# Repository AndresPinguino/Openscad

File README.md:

# Openscad
Modelos 3D parametricos

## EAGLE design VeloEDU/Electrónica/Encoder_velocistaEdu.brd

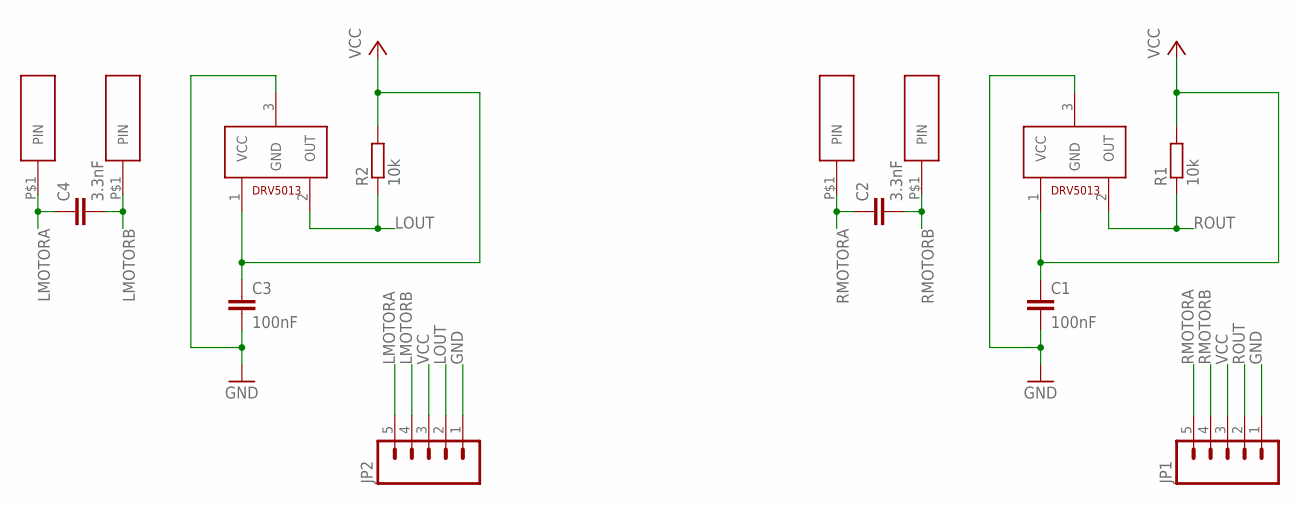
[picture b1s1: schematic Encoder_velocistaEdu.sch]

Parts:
C1, C3: 100nF; C0805
C2, C4: 3.3nF; C0805
JP1, JP2: M05PTH; 1X05
R1, R2: 10k; M0805
U$1, U$6: DRV5013; DBZ_R-PDSO-G3
U$2, U$3, U$4, U$5: TERMINAL_MOTOR_N20

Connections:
GND: C1.2, C3.2, JP1.1, JP2.1, U$1.3 (GND), U$6.3 (GND)
LMOTORA: C4.1, JP2.5, U$4.P$1
LMOTORB: C4.2, JP2.4, U$5.P$1
LOUT: JP2.2, R2.1, U$6.2 (OUT)
RMOTORA: C2.1, JP1.5, U$2.P$1
RMOTORB: C2.2, JP1.4, U$3.P$1
ROUT: JP1.2, R1.1, U$1.2 (OUT)
VCC: C1.1, C3.1, JP1.3, JP2.3, R1.2, R2.2, U$1.1 (VCC), U$6.1 (VCC)

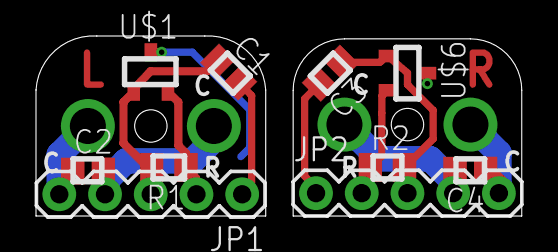
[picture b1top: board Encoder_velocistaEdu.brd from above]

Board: 2 copper layers, 27.0 x 10.0 mm, 14 parts (0 on the bottom side), 8 nets.

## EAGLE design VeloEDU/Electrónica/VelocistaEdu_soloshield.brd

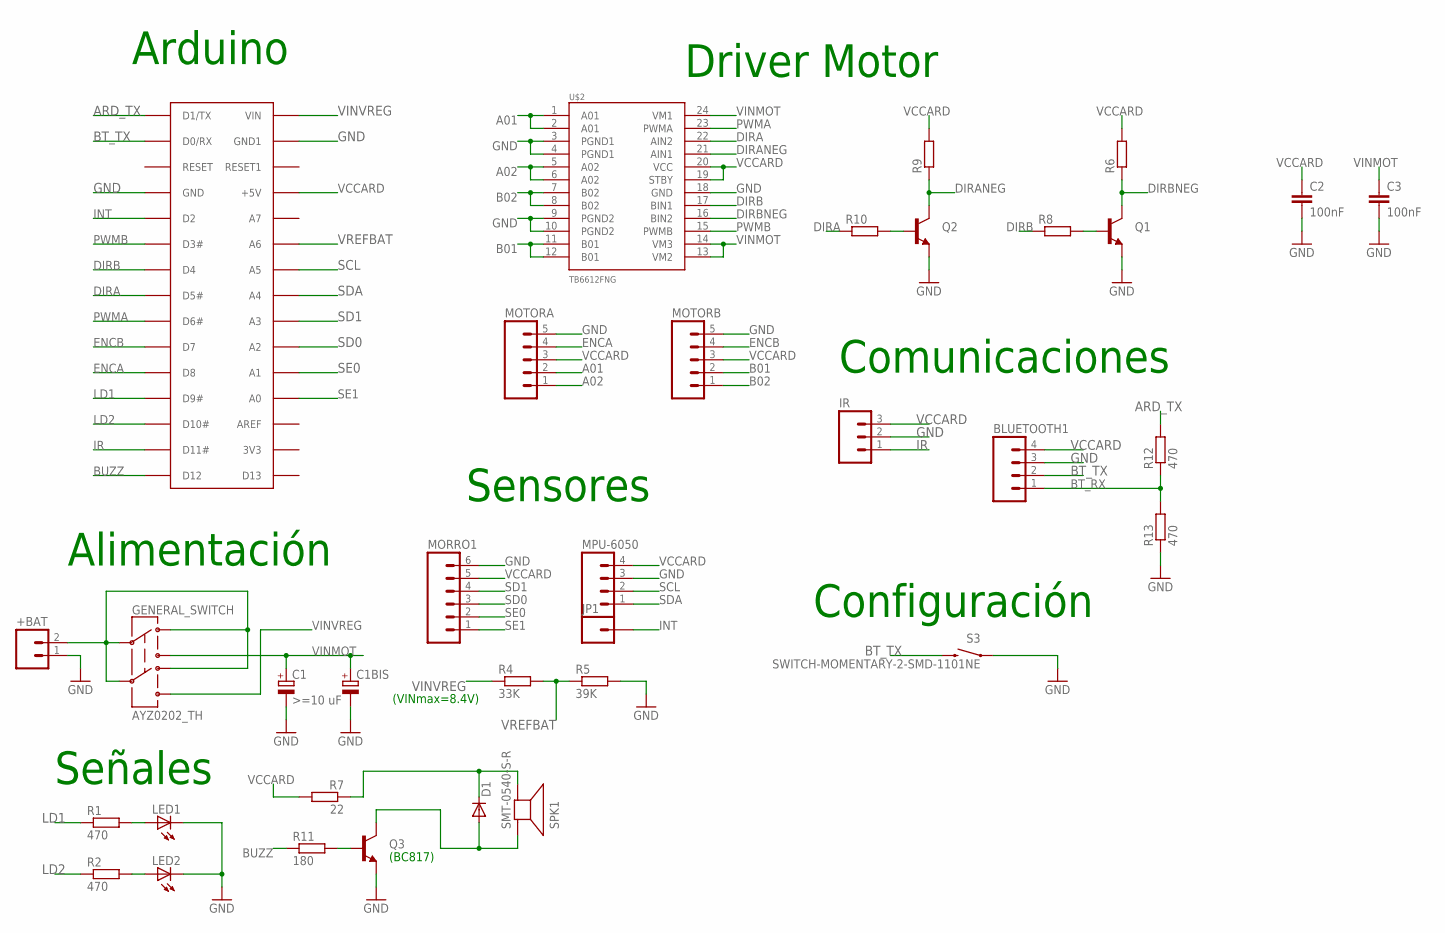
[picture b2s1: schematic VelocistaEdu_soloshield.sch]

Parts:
+BAT: M02LOCK_LONGPADS; 1X02_LOCK_LONGPADS
BLUETOOTH1: M04LONGPADS; 1X04_LONGPADS
C1: >=10 uF; SMC_C
C1BIS: CPOL-EUE2.5-5; E2,5-5
C2, C3: 100nF; C0805
D1: DIODE-MICROMELF-W; MICROMELF-W
GENERAL_SWITCH: AYZ0202_TH
IR: M03LONGPADS; 1X03_LONGPADS
JP1: M01PTH_LONGPAD; 1X01_LONGPAD
LED1, LED2: LEDCHIPLED_0805; CHIPLED_0805
MORRO1: M06LONGPADS; 1X06_LONGPADS
MOTORA: M05PTH; 1X05
MOTORB: M05PTH; 1X05
MPU-6050: M04LONGPADS; 1X04_LONGPADS
Q1, Q2, Q3: TRANSISTOR_NPNSOT23; SOT23
R1, R2, R12, R13: 470; R0805
R4: 33K; R0805
R5: 39K; R0805
R6, R8, R9, R10: R-EU_M0805; M0805
R7: 22; R0805
R11: 180; M0805
S3: SWITCH-MOMENTARY-2-SMD-1101NE; TACTILE-SWITCH-1101NE
SPK1: SMT-0540-S-R
U$1: ARDUINONANONOHOLES; PDIP-32NOHOLES
U$2: TB6612FNG; SSOP24

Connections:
A01: MOTORA.2, U$2.1 (A01), U$2.2 (A01)
A02: MOTORA.1, U$2.5 (A02), U$2.6 (A02)
ARD_TX: R12.2, U$1.D1/TX
B01: MOTORB.2, U$2.11 (B01), U$2.12 (B01)
B02: MOTORB.1, U$2.7 (B02), U$2.8 (B02)
BT_RX: BLUETOOTH1.1, R12.1, R13.2
BT_TX: BLUETOOTH1.2, S3.P$2 (2), U$1.D0/RX
BUZZ: R11.1, U$1.D12
DIRA: R10.1, U$1.D5 (D5#), U$2.22 (AIN2)
DIRANEG: Q2.3 (C), R9.1, U$2.21 (AIN1)
DIRB: R8.1, U$1.D4, U$2.17 (BIN1)
DIRBNEG: Q1.3 (C), R6.1, U$2.16 (BIN2)
ENCA: MOTORA.4, U$1.D8
ENCB: MOTORB.4, U$1.D7
GND: +BAT.1, BLUETOOTH1.3, C1.-, C1BIS.-, C2.2, C3.2, IR.2, LED1.C, LED2.C, MORRO1.6, MOTORA.5, MOTORB.5, MPU-6050.3, Q1.2 (E), Q2.2 (E), Q3.2 (E), R5.2, R13.1, S3.P$1 (1), U$1.GND, U$1.GND1, U$2.3 (PGND1), U$2.4 (PGND1), U$2.9 (PGND2), U$2.10 (PGND2), U$2.18 (GND)
INT: JP1.1, U$1.D2
IR: IR.1, U$1.D11 (D11#)
LD1: R1.1, U$1.D9 (D9#)
LD2: R2.1, U$1.D10 (D10#)
unnamed: +BAT.2, GENERAL_SWITCH.C1, GENERAL_SWITCH.C2, GENERAL_SWITCH.D1, GENERAL_SWITCH.D2
unnamed: LED1.A, R1.2
unnamed: D1.C, R7.1, SPK1.+ (-)
unnamed: LED2.A, R2.2
unnamed: Q2.1 (B), R10.2
unnamed: Q3.1 (B), R11.2
unnamed: D1.A, Q3.3 (C), SPK1.- (+)
unnamed: Q1.1 (B), R8.2
PWMA: U$1.D6 (D6#), U$2.23 (PWMA)
PWMB: U$1.D3 (D3#), U$2.15 (PWMB)
SCL: MPU-6050.2, U$1.A5
SD0: MORRO1.3, U$1.A2
SD1: MORRO1.4, U$1.A3
SDA: MPU-6050.1, U$1.A4
SE0: MORRO1.2, U$1.A1
SE1: MORRO1.1, U$1.A0
VCCARD: BLUETOOTH1.4, C2.1, IR.3, MORRO1.5, MOTORA.3, MOTORB.3, MPU-6050.4, R6.2, R7.2, R9.2, U$1.+5V, U$2.19 (STBY), U$2.20 (VCC)
VINMOT: C1.+, C1BIS.+, C3.1, GENERAL_SWITCH.B1, U$2.13 (VM2), U$2.14 (VM3), U$2.24 (VM1)
VINVREG: GENERAL_SWITCH.B2, R4.1, U$1.VIN
VREFBAT: R4.2, R5.1, U$1.A6

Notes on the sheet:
Alimentación
Sensores
Señales
Comunicaciones
Configuración
Arduino
Driver Motor
(VINmax=8.4V)
(BC817)

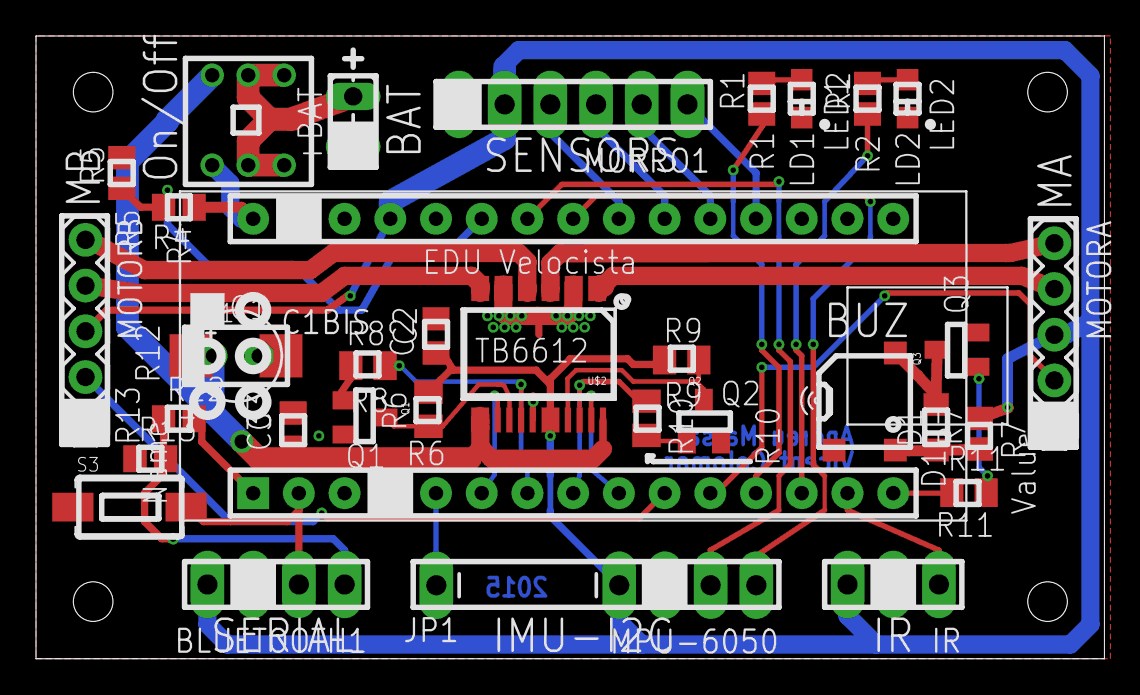
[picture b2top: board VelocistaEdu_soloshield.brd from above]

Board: 2 copper layers, 59.4 x 34.6 mm, 35 parts (0 on the bottom side), 39 nets.

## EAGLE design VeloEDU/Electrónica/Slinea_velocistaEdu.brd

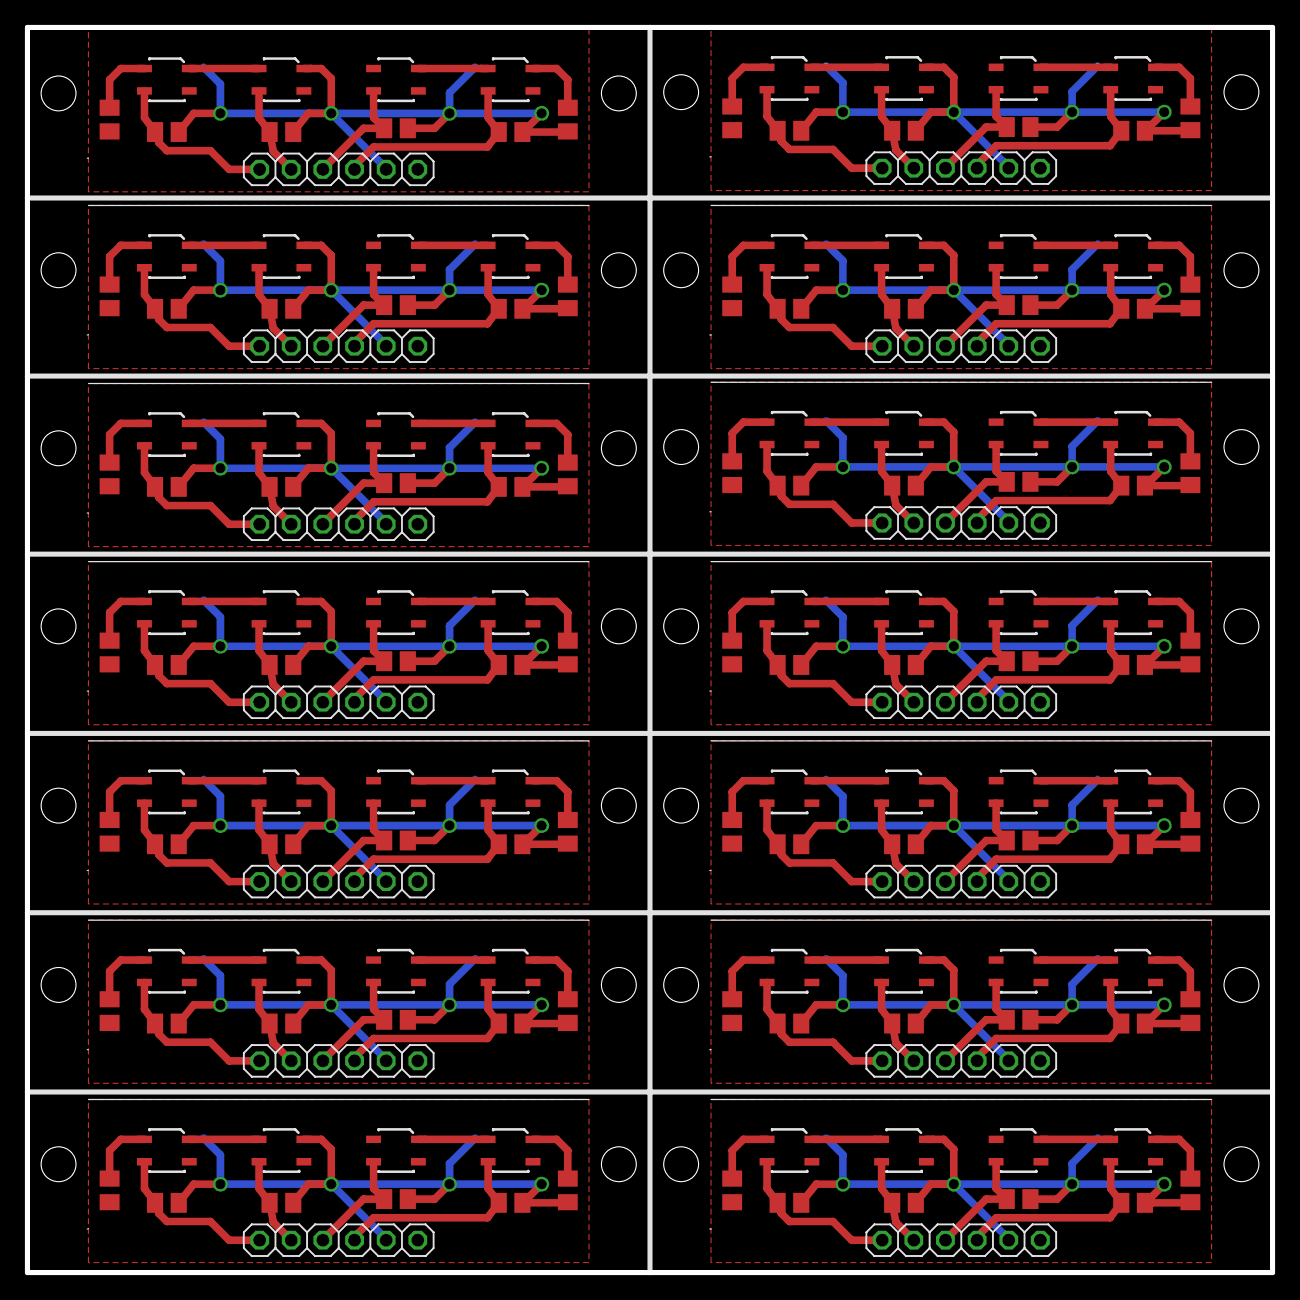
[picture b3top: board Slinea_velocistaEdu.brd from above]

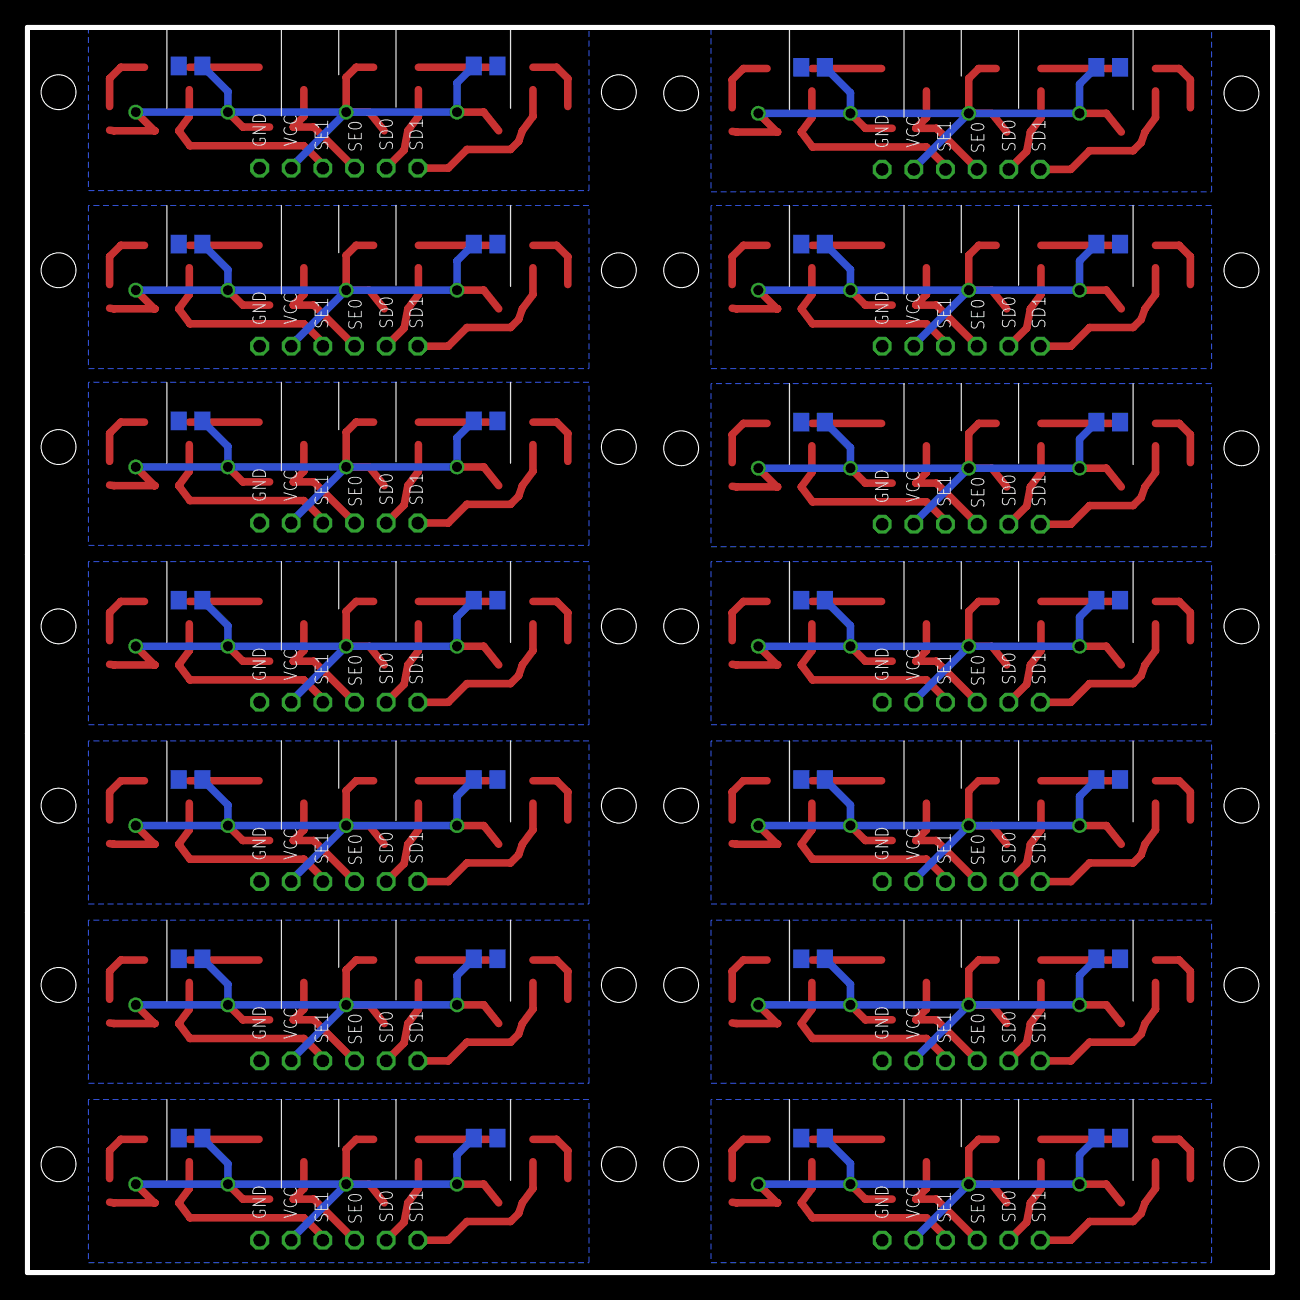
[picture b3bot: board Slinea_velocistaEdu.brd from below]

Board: 2 copper layers, 100.0 x 100.0 mm, 182 parts (28 on the bottom side), 140 nets.

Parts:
CS1, CS2, CS3, CS4, CS5, CS6, CS7, CS8, CS9, CS10, CS11, CS12, CS13, CS14, CS15, CS16, CS17, CS18, CS19, CS20, CS21, CS22, CS23, CS24, CS25, CS26, CS27, CS28: C0805
JP1, JP2, JP3, JP4, JP5, JP6, JP7, JP8, JP9, JP10, JP11, JP12, JP13, JP14: 1X06
R1, R2, R3, R4, R5, R6, R7, R8, R9, R10, R11, R12, R13, R14, R15, R16, R17, R18, R19, R20, R21, R22, R23, R24, R25, R26, R27, R28, R29, R30, R31, R32, R33, R34, R35, R36, R37, R38, R39, R40, R41, R42, R43, R44, R45, R46, R47, R48, R49, R50, R51, R52, R53, R54, R55, R56: M0805
RP1, RP2, RP3, RP4, RP5, RP6, RP7, RP8, RP9, RP10, RP11, RP12, RP13, RP14, RP15, RP16, RP17, RP18, RP19, RP20, RP21, RP22, RP23, RP24, RP25, RP26, RP27, RP28: M0805
U$1, U$2, U$3, U$4, U$5, U$6, U$7, U$8, U$9, U$10, U$11, U$12, U$13, U$14, U$15, U$16, U$17, U$18, U$19, U$20, U$21, U$22, U$23, U$24, U$25, U$26, U$27, U$28, U$29, U$30, U$31, U$32, U$33, U$34, U$35, U$36, U$37, U$38, U$39, U$40, U$41, U$42, U$43, U$44, U$45, U$46, U$47, U$48, U$49, U$50, U$51, U$52, U$53, U$54, U$55, U$56: QRE1113

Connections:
+VS1: CS1.1, CS2.1, JP1.5, R1.2, R2.2, R3.2, R4.2, RP1.2, U$5.1
+VS2: CS3.1, CS4.1, JP10.5, R20.2, R21.2, R22.2, R23.2, RP3.2, U$7.1
+VS3: CS5.1, CS6.1, JP2.5, R5.2, R6.2, R7.2, R8.2, RP5.2, U$11.1
+VS4: CS7.1, CS8.1, JP3.5, R9.2, R10.2, R11.2, R12.2, RP7.2, U$15.1
+VS5: CS9.1, CS10.1, JP4.5, R13.2, R14.2, R15.2, R16.2, RP9.2, U$19.1
+VS6: CS11.1, CS12.1, JP5.5, R17.2, R18.2, R19.2, R24.2, RP11.2, U$23.1
+VS7: CS13.1, CS14.1, JP6.5, R25.2, R26.2, R27.2, R28.2, RP13.2, U$27.1
+VS8: CS15.1, CS16.1, JP7.5, R29.2, R30.2, R31.2, R32.2, RP15.2, U$31.1
+VS9: CS17.1, CS18.1, JP8.5, R33.2, R34.2, R35.2, R36.2, RP17.2, U$35.1
+VS10: CS19.1, CS20.1, JP9.5, R37.2, R38.2, R39.2, R40.2, RP19.2, U$39.1
+VS11: CS21.1, CS22.1, JP11.5, R41.2, R42.2, R43.2, R44.2, RP21.2, U$43.1
+VS12: CS23.1, CS24.1, JP12.5, R45.2, R46.2, R47.2, R48.2, RP23.2, U$47.1
+VS13: CS25.1, CS26.1, JP13.5, R49.2, R50.2, R51.2, R52.2, RP25.2, U$51.1
+VS14: CS27.1, CS28.1, JP14.5, R53.2, R54.2, R55.2, R56.2, RP27.2, U$55.1
GNDS1: CS1.2, CS2.2, JP1.6, RP2.1, U$1.4, U$3.2, U$3.4, U$5.4, U$6.4
GNDS2: CS3.2, CS4.2, JP10.6, RP4.1, U$2.4, U$4.2, U$4.4, U$7.4, U$10.4
GNDS3: CS5.2, CS6.2, JP2.6, RP6.1, U$8.4, U$9.2, U$9.4, U$11.4, U$12.4
GNDS4: CS7.2, CS8.2, JP3.6, RP8.1, U$13.4, U$14.2, U$14.4, U$15.4, U$16.4
GNDS5: CS9.2, CS10.2, JP4.6, RP10.1, U$17.4, U$18.2, U$18.4, U$19.4, U$20.4
GNDS6: CS11.2, CS12.2, JP5.6, RP12.1, U$21.4, U$22.2, U$22.4, U$23.4, U$24.4
GNDS7: CS13.2, CS14.2, JP6.6, RP14.1, U$25.4, U$26.2, U$26.4, U$27.4, U$28.4
GNDS8: CS15.2, CS16.2, JP7.6, RP16.1, U$29.4, U$30.2, U$30.4, U$31.4, U$32.4
GNDS9: CS17.2, CS18.2, JP8.6, RP18.1, U$33.4, U$34.2, U$34.4, U$35.4, U$36.4
GNDS10: CS19.2, CS20.2, JP9.6, RP20.1, U$37.4, U$38.2, U$38.4, U$39.4, U$40.4
GNDS11: CS21.2, CS22.2, JP11.6, RP22.1, U$41.4, U$42.2, U$42.4, U$43.4, U$44.4
GNDS12: CS23.2, CS24.2, JP12.6, RP24.1, U$45.4, U$46.2, U$46.4, U$47.4, U$48.4
GNDS13: CS25.2, CS26.2, JP13.6, RP26.1, U$49.4, U$50.2, U$50.4, U$51.4, U$52.4
GNDS14: CS27.2, CS28.2, JP14.6, RP28.1, U$53.4, U$54.2, U$54.4, U$55.4, U$56.4
unnamed: U$1.2, U$3.1
unnamed: U$5.2, U$6.1
unnamed: RP2.2, U$6.2
unnamed: RP1.1, U$1.1
unnamed: U$8.2, U$9.1
unnamed: U$11.2, U$12.1
unnamed: RP6.2, U$12.2
unnamed: RP5.1, U$8.1
unnamed: U$13.2, U$14.1
unnamed: U$15.2, U$16.1
unnamed: RP8.2, U$16.2
unnamed: RP7.1, U$13.1
unnamed: U$17.2, U$18.1
unnamed: U$19.2, U$20.1
unnamed: RP10.2, U$20.2
unnamed: RP9.1, U$17.1
unnamed: U$21.2, U$22.1
unnamed: U$23.2, U$24.1
unnamed: RP12.2, U$24.2
unnamed: RP11.1, U$21.1
unnamed: U$25.2, U$26.1
unnamed: U$27.2, U$28.1
unnamed: RP14.2, U$28.2
unnamed: RP13.1, U$25.1
unnamed: U$29.2, U$30.1
unnamed: U$31.2, U$32.1
unnamed: RP16.2, U$32.2
unnamed: RP15.1, U$29.1
unnamed: U$33.2, U$34.1
unnamed: U$35.2, U$36.1
unnamed: RP18.2, U$36.2
unnamed: RP17.1, U$33.1
unnamed: U$37.2, U$38.1
unnamed: U$39.2, U$40.1
unnamed: RP20.2, U$40.2
unnamed: RP19.1, U$37.1
unnamed: U$41.2, U$42.1
unnamed: U$43.2, U$44.1
unnamed: RP22.2, U$44.2
unnamed: RP21.1, U$41.1
unnamed: U$45.2, U$46.1
unnamed: U$47.2, U$48.1
unnamed: RP24.2, U$48.2
unnamed: RP23.1, U$45.1
unnamed: U$49.2, U$50.1
unnamed: U$51.2, U$52.1
unnamed: RP26.2, U$52.2
unnamed: RP25.1, U$49.1
unnamed: U$53.2, U$54.1
unnamed: U$55.2, U$56.1
unnamed: RP28.2, U$56.2
unnamed: RP27.1, U$53.1
unnamed: U$2.2, U$4.1
unnamed: U$7.2, U$10.1
unnamed: RP4.2, U$10.2
unnamed: RP3.1, U$2.1
SD0+: JP10.2, R22.1, U$7.3
SD0+1: JP1.2, R3.1, U$5.3
SD0+2: JP2.2, R7.1, U$11.3
SD0+3: JP3.2, R11.1, U$15.3
SD0+4: JP4.2, R15.1, U$19.3
SD0+5: JP5.2, R19.1, U$23.3
SD0+6: JP6.2, R27.1, U$27.3
SD0+7: JP7.2, R31.1, U$31.3
SD0+8: JP8.2, R35.1, U$35.3
SD0+9: JP9.2, R39.1, U$39.3
SD0+10: JP11.2, R43.1, U$43.3
SD0+11: JP12.2, R47.1, U$47.3
SD0+12: JP13.2, R51.1, U$51.3
SD0+13: JP14.2, R55.1, U$55.3
SD1+: JP10.1, R23.1, U$10.3
SD1+1: JP1.1, R4.1, U$6.3
SD1+2: JP2.1, R8.1, U$12.3
SD1+3: JP3.1, R12.1, U$16.3
SD1+4: JP4.1, R16.1, U$20.3
SD1+5: JP5.1, R24.1, U$24.3
SD1+6: JP6.1, R28.1, U$28.3
SD1+7: JP7.1, R32.1, U$32.3
SD1+8: JP8.1, R36.1, U$36.3
SD1+9: JP9.1, R40.1, U$40.3
SD1+10: JP11.1, R44.1, U$44.3
SD1+11: JP12.1, R48.1, U$48.3
SD1+12: JP13.1, R52.1, U$52.3
SD1+13: JP14.1, R56.1, U$56.3
SE0+: JP10.3, R21.1, U$4.3
SE0+1: JP1.3, R2.1, U$3.3
SE0+2: JP2.3, R6.1, U$9.3
SE0+3: JP3.3, R10.1, U$14.3
SE0+4: JP4.3, R14.1, U$18.3
SE0+5: JP5.3, R18.1, U$22.3
SE0+6: JP6.3, R26.1, U$26.3
SE0+7: JP7.3, R30.1, U$30.3
SE0+8: JP8.3, R34.1, U$34.3
SE0+9: JP9.3, R38.1, U$38.3
SE0+10: JP11.3, R42.1, U$42.3
SE0+11: JP12.3, R46.1, U$46.3
SE0+12: JP13.3, R50.1, U$50.3
SE0+13: JP14.3, R54.1, U$54.3
SE1+: JP10.4, R20.1, U$2.3
SE1+1: JP1.4, R1.1, U$1.3
SE1+2: JP2.4, R5.1, U$8.3
SE1+3: JP3.4, R9.1, U$13.3
SE1+4: JP4.4, R13.1, U$17.3
SE1+5: JP5.4, R17.1, U$21.3
SE1+6: JP6.4, R25.1, U$25.3
SE1+7: JP7.4, R29.1, U$29.3
SE1+8: JP8.4, R33.1, U$33.3
SE1+9: JP9.4, R37.1, U$37.3
SE1+10: JP11.4, R41.1, U$41.3
SE1+11: JP12.4, R45.1, U$45.3
SE1+12: JP13.4, R49.1, U$49.3
SE1+13: JP14.4, R53.1, U$53.3

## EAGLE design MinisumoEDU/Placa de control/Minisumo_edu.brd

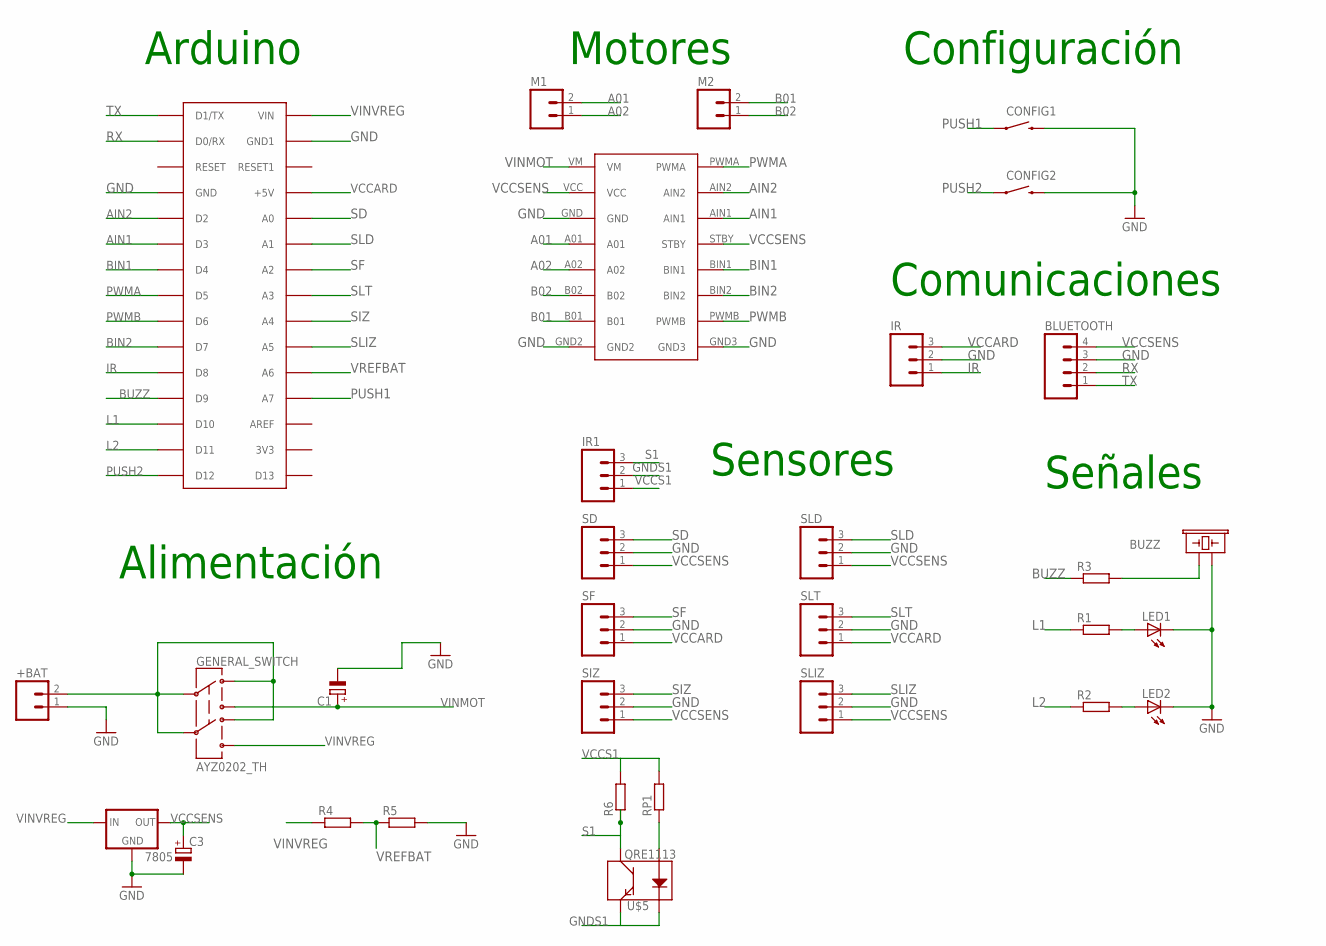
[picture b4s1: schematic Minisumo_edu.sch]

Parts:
7805: V_REG_78XXSINK; TO220-IGO
+BAT: M02LOCK_LONGPADS; 1X02_LOCK_LONGPADS
BLUETOOTH: M04LONGPADS; 1X04_LONGPADS
BUZZ: BUZZERPTH; BUZZER-12MM
C1, C3: CPOL-EUE2.5-6; E2,5-6
CONFIG1, CONFIG2: SWITCH-MOMENTARY-2PTH; TACTILE-PTH
GENERAL_SWITCH: AYZ0202_TH
IR, IR1: M03LONGPADS; 1X03_LONGPADS
LED1, LED2: LED3MM
M1, M2: M02LOCK_LONGPADS; 1X02_LOCK_LONGPADS
R1, R2, R3, R4, R5: R-EU_0207/7; 0207/7
R6: R-EU_M0805; M0805@1
RP1: R-EU_M0805; M0805
SD: M03LONGPADS; 1X03_LONGPADS
SF: M03LONGPADS; 1X03_LONGPADS
SIZ: M03LONGPADS; 1X03_LONGPADS
SLD: M03LONGPADS; 1X03_LONGPADS
SLIZ: M03LONGPADS; 1X03_LONGPADS
SLT: M03LONGPADS; 1X03_LONGPADS
U$1: ARDUINONANO; PDIP-32
U$3: TB6612FNG_SPARKFUN
U$5: QRE1113

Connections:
A01: M1.2, U$3.A01
A02: M1.1, U$3.A02
AIN1: U$1.D3, U$3.AIN1
AIN2: U$1.D2, U$3.AIN2
B01: M2.2, U$3.B01
B02: M2.1, U$3.B02
BIN1: U$1.D4, U$3.BIN1
BIN2: U$1.D7, U$3.BIN2
BUZZ: R3.1, U$1.D9
GND: 7805.GND, +BAT.1, BLUETOOTH.3, BUZZ.- (2), C1.-, C3.-, CONFIG1.3 (2), CONFIG2.3 (2), IR.2, LED1.K (C), LED2.K (C), R5.2, SD.2, SF.2, SIZ.2, SLD.2, SLIZ.2, SLT.2, U$1.GND, U$1.GND1, U$3.GND, U$3.GND2, U$3.GND3
GNDS1: IR1.2, U$5.2 (K), U$5.4 (E)
IR: IR.1, U$1.D8
L1: R1.1, U$1.D10
L2: R2.1, U$1.D11
unnamed: +BAT.2, GENERAL_SWITCH.C1, GENERAL_SWITCH.C2, GENERAL_SWITCH.D1, GENERAL_SWITCH.D2
unnamed: LED1.A, R1.2
unnamed: BUZZ.+ (1), R3.2
unnamed: LED2.A, R2.2
unnamed: RP1.1, U$5.1 (A)
PUSH1: CONFIG1.1, U$1.A7
PUSH2: CONFIG2.1, U$1.D12
PWMA: U$1.D5, U$3.PWMA
PWMB: U$1.D6, U$3.PWMB
RX: BLUETOOTH.2, U$1.D0/RX
S1: IR1.3, R6.1, U$5.3 (C)
SD: SD.3, U$1.A0
SF: SF.3, U$1.A2
SIZ: SIZ.3, U$1.A4
SLD: SLD.3, U$1.A1
SLIZ: SLIZ.3, U$1.A5
SLT: SLT.3, U$1.A3
TX: BLUETOOTH.1, U$1.D1/TX
VCCARD: IR.3, SF.1, SLT.1, U$1.+5V
VCCS1: IR1.1, R6.2, RP1.2
VCCSENS: 7805.OUT, BLUETOOTH.4, C3.+, SD.1, SIZ.1, SLD.1, SLIZ.1, U$3.STBY, U$3.VCC
VINMOT: C1.+, GENERAL_SWITCH.B1, U$3.VM
VINVREG: 7805.IN, GENERAL_SWITCH.B2, R4.1, U$1.VIN
VREFBAT: R4.2, R5.1, U$1.A6

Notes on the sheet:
Alimentación
Sensores
Señales
Comunicaciones
Configuración
Arduino
Motores

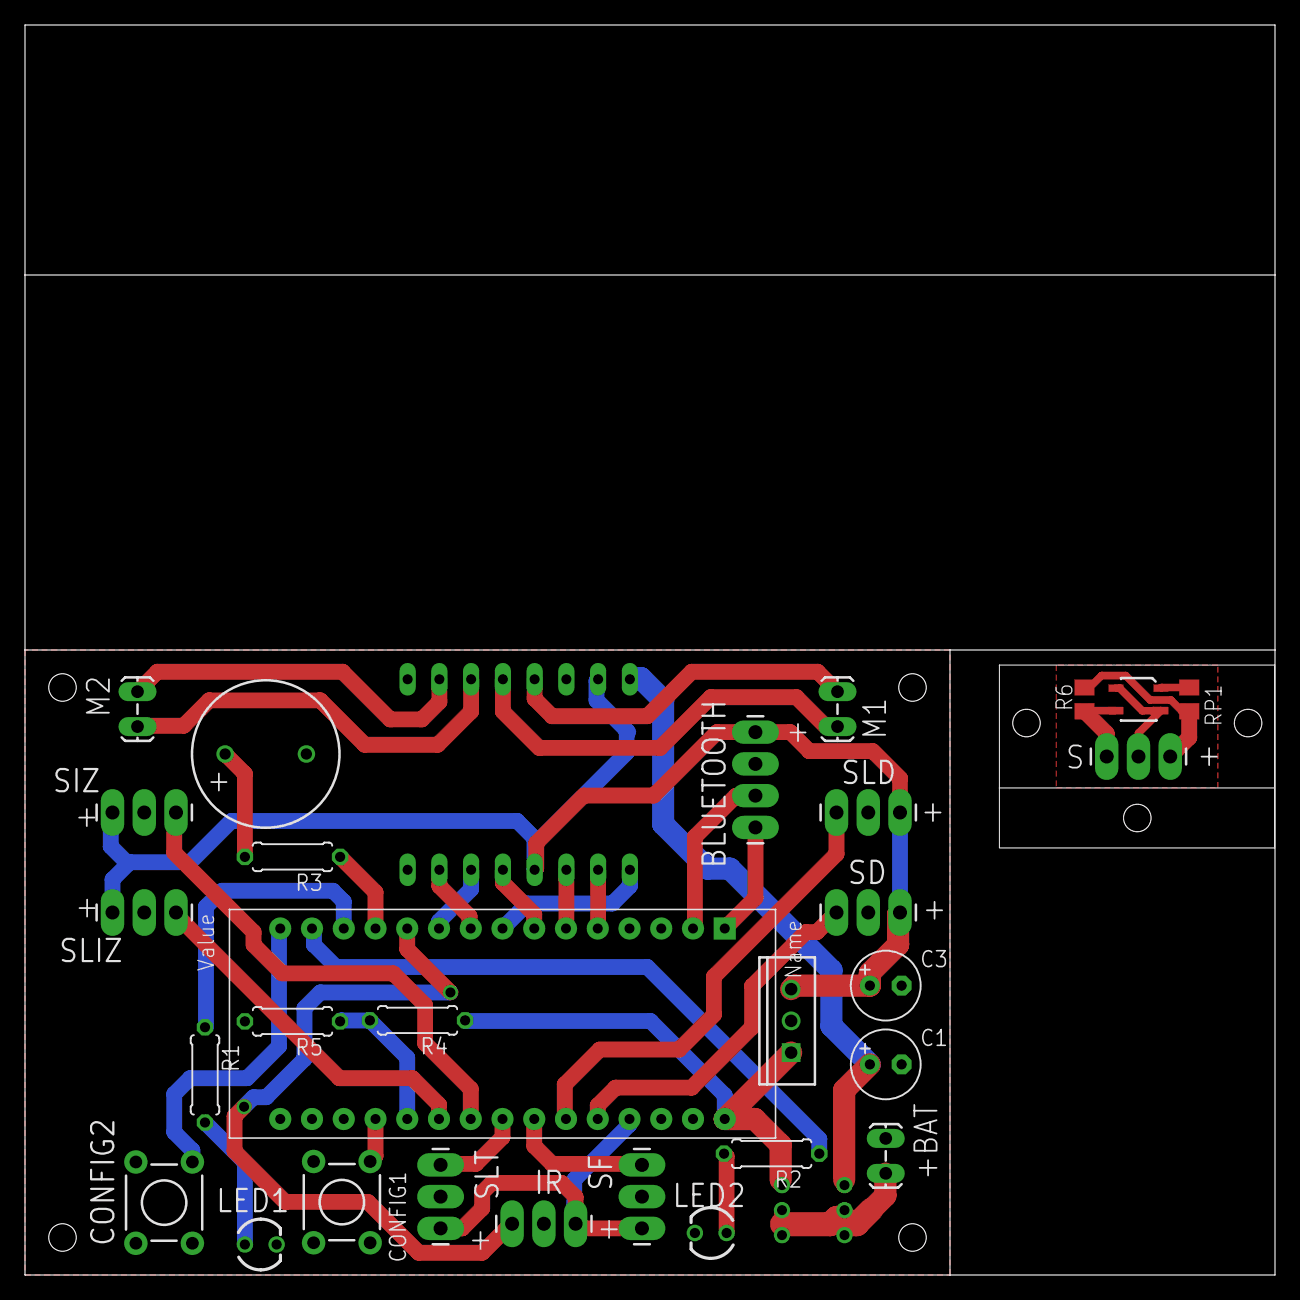
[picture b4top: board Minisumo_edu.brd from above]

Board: 2 copper layers, 100.0 x 100.0 mm, 31 parts (0 on the bottom side), 38 nets.

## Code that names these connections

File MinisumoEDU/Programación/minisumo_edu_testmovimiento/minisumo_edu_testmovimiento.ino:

/*
Test de los motores:
cuando apretamos cualquier pulsador:
adelante
atras
giro derecha
giro izquierda
pivota en sentido horario
pivota en sentido antihorario

*/




#define SD A7
#define SLD A6
#define SF A5
#define SLT A4
#define SIZ A3
#define SLIZ A2
#define VREF A1
#define PUSH1 A0
#define AIN2 2
#define AIN1 3
#define BIN1 4
#define PWMA 5
#define PWMB 6
#define BIN2 7
#define IR 8
#define BUZZ 9
#define Led1 10
#define Led2 11
#define PUSH2 12
#define Led3 13


volatile int velocidad=50;

void setup() {
  //Entradas
pinMode(PUSH1,INPUT_PULLUP);
pinMode(PUSH2,INPUT_PULLUP);
pinMode(SF,INPUT);
pinMode(SLT,INPUT);
pinMode(SIZ,INPUT);
pinMode(SLIZ,INPUT);
pinMode(IR,INPUT);

// Salidas
pinMode(Led1,OUTPUT);
pinMode(Led2,OUTPUT);
pinMode(Led3,OUTPUT);
pinMode(BUZZ,OUTPUT);
pinMode(AIN1,OUTPUT);
pinMode(AIN2,OUTPUT);
pinMode(BIN1,OUTPUT);
pinMode(BIN2,OUTPUT);
pinMode(PWMA,OUTPUT);
pinMode(PWMB,OUTPUT);


}
void loop() {
 while (digitalRead(PUSH1)&&digitalRead(PUSH2));
 bip(1);
 delay(1000);
 bip(0);
 delay(500);

   adelante();
   delay(1000);
   para();
   delay(200);
   atras();
   delay(1000);
   para();
   delay(200);
   giro_derecha();
   delay(1000);
   para();
   delay(200);
   giro_izquierda();
   delay(1000);
   para();
   delay(200);
   pivota_h();
   delay(1000);
      para();
   delay(200);
   pivota_ah();
   delay(1000);
      para();
   delay(200);

 
}

void led_on(char nled)
{
    switch (nled) {
  case 0:    // your hand is on the sensor
    digitalWrite(Led1,HIGH);
    break;
  case 1:    // your hand is close to the sensor
    digitalWrite(Led2,HIGH);
    break;
  case 2:    // your hand is a few inches from the sensor
    digitalWrite(Led3,HIGH);
    break;
    }
}

void led_off(char nled)
{
    switch (nled) {
  case 0:    // your hand is on the sensor
    digitalWrite(Led1,LOW);
    break;
  case 1:    // your hand is close to the sensor
    digitalWrite(Led2,LOW);
    break;
  case 2:    // your hand is a few inches from the sensor
    digitalWrite(Led3,LOW);
    break;
    }
}

void bip(char estat)
{
 if (estat==1)
    digitalWrite(BUZZ,HIGH); // canviar 13 -- BUZZ
 else
    digitalWrite(BUZZ,LOW); 
}

void adelante(void)
{
 digitalWrite(AIN2,HIGH);
 digitalWrite(AIN1,LOW);
 analogWrite(PWMA,velocidad);
  digitalWrite(BIN1,HIGH);
 digitalWrite(BIN2,LOW);
 analogWrite(PWMB,velocidad);
}

void atras(void)
{
 digitalWrite(AIN1,HIGH);
 digitalWrite(AIN2,LOW);
 analogWrite(PWMA,velocidad);
 digitalWrite(BIN2,HIGH);
 digitalWrite(BIN1,LOW);
 analogWrite(PWMB,velocidad);
  
}
void giro_derecha(void)
{
   digitalWrite(AIN2,HIGH);
 digitalWrite(AIN1,LOW);
 analogWrite(PWMA,0);
  digitalWrite(BIN1,HIGH);
 digitalWrite(BIN2,LOW);
 analogWrite(PWMB,velocidad);
  
}

void giro_izquierda(void)
{
   digitalWrite(AIN2,HIGH);
 digitalWrite(AIN1,LOW);
 analogWrite(PWMA,velocidad);
  digitalWrite(BIN1,HIGH);
 digitalWrite(BIN2,LOW);
 analogWrite(PWMB,0);
}

void pivota_h(void)
{
  digitalWrite(AIN1,HIGH);
 digitalWrite(AIN2,LOW);
 analogWrite(PWMA,velocidad);
  digitalWrite(BIN1,HIGH);
 digitalWrite(BIN2,LOW);
 analogWrite(PWMB,velocidad); 
}

void pivota_ah()
{
  digitalWrite(AIN2,HIGH);
 digitalWrite(AIN1,LOW);
 analogWrite(PWMA,velocidad);
  digitalWrite(BIN2,HIGH);
 digitalWrite(BIN1,LOW);
 analogWrite(PWMB,velocidad); 
}

void para(void)
{
  digitalWrite(AIN1,HIGH);
 digitalWrite(AIN2,LOW);
 analogWrite(PWMA,0);
   digitalWrite(BIN1,HIGH);
 digitalWrite(BIN2,LOW);
 analogWrite(PWMB,0);
  
}

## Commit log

2018-07-02 modelado 3D parametrico
2018-07-29 Llantas de SUMO
2018-07-31 rueda para hub4wd
2018-08-01 seguidor de línea
2018-08-06 modelos 3D
2018-08-13 ruedas 70mm x 8 mm para pegar
2018-08-15 rueda con centro grande

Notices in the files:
parts and their libraries:
SparkFun: Licensing: CC v3.0 Share-Alike You are welcome to use this library for commercial purposes.
SparkFun-PowerIC: Licensing: Creative Commons ShareAlike 4.0 International - https://creativecommons.org/licenses/by-sa/4.0
